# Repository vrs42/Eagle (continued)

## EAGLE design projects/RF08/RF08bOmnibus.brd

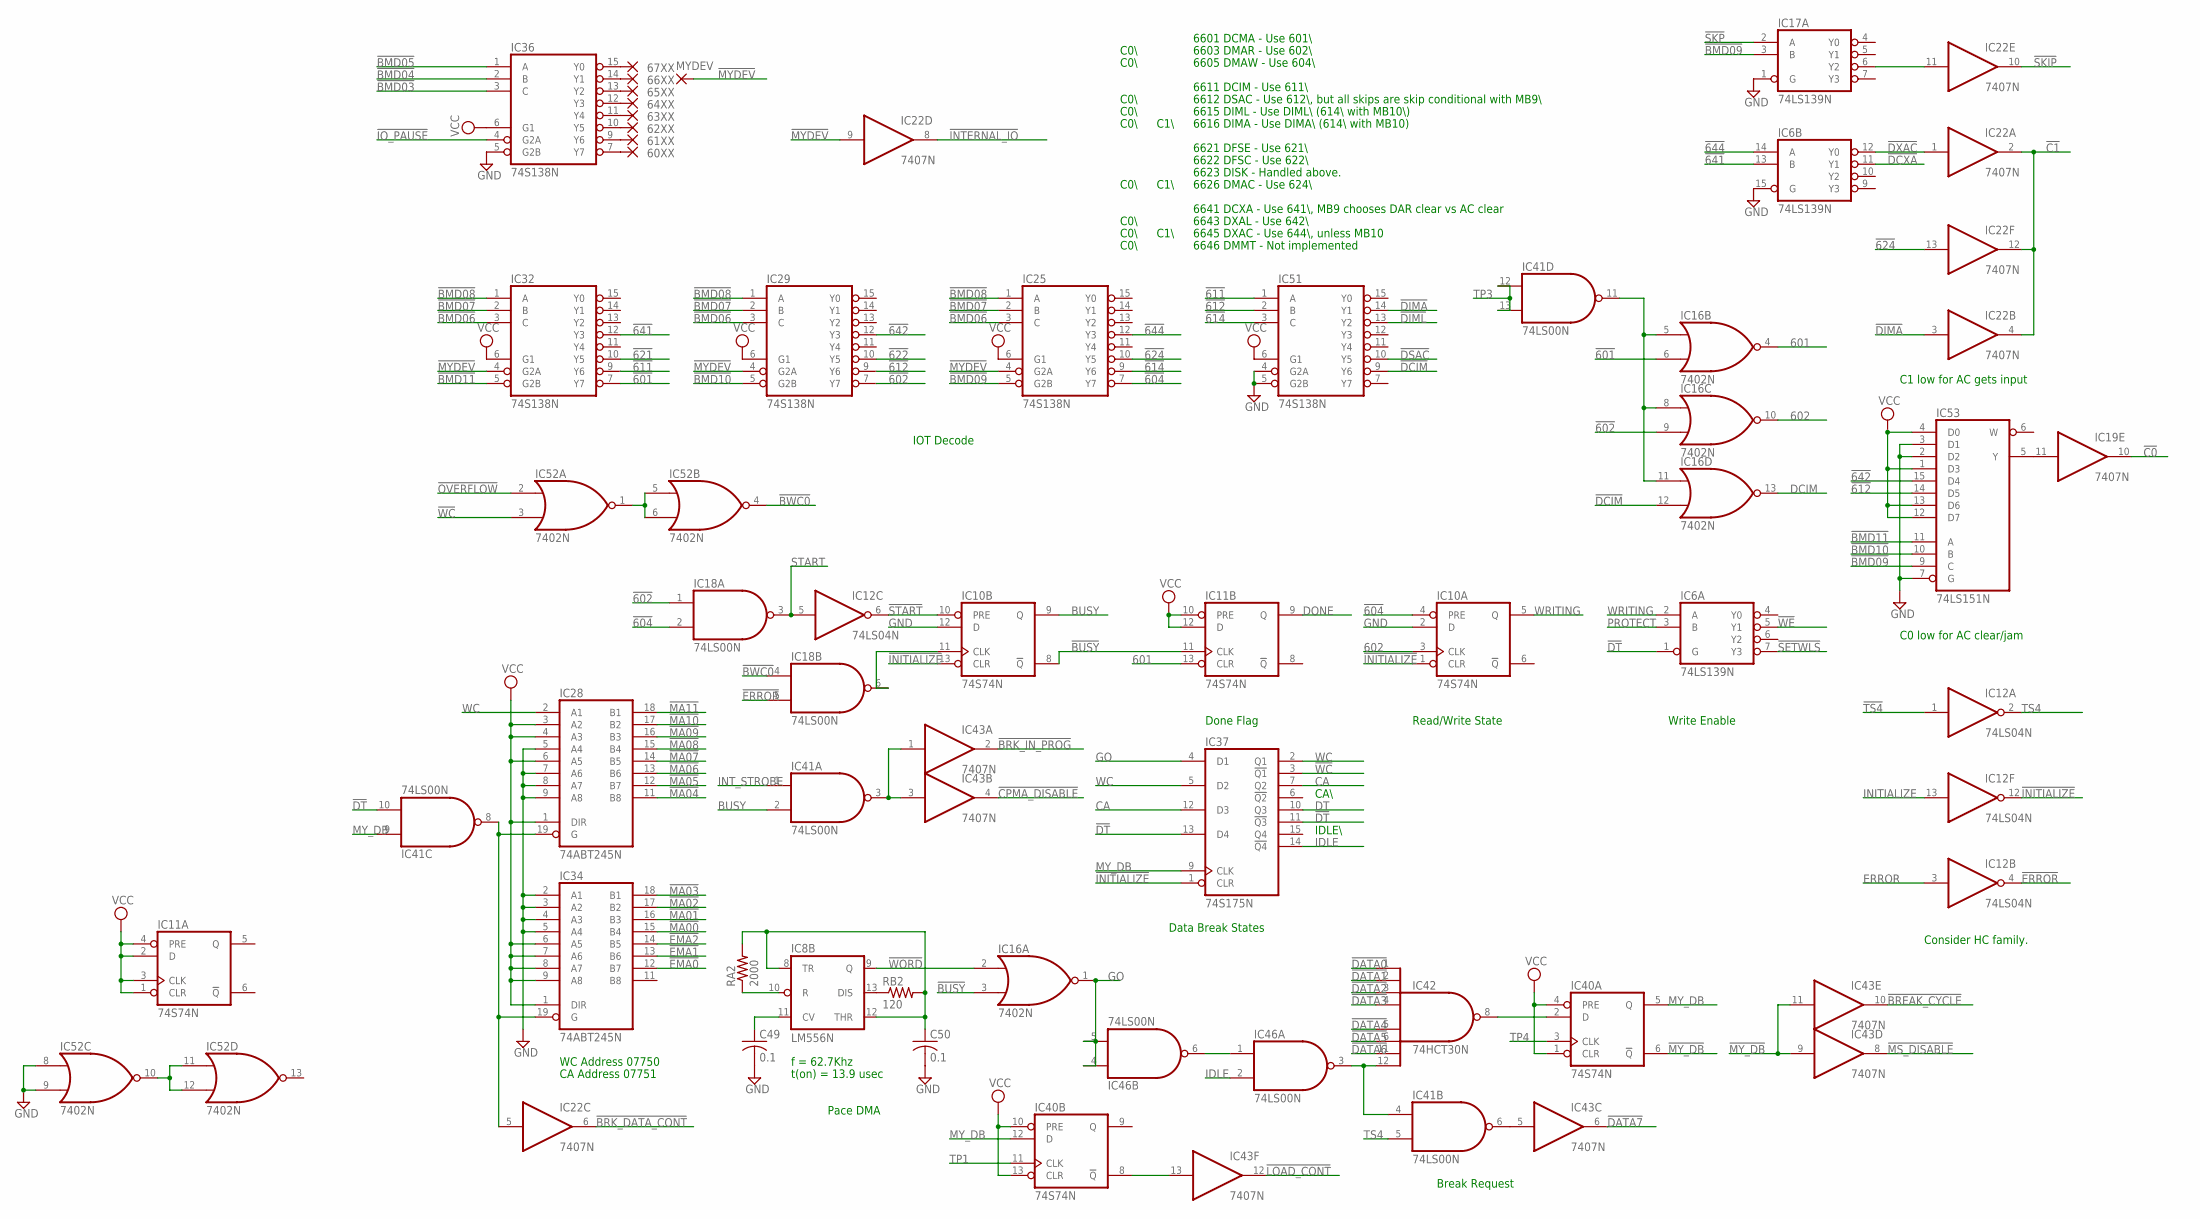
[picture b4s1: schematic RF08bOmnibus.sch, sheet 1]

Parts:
60XX, 61XX, 62XX, 63XX, 64XX, 65XX, 66XX, 67XX: 1,6/0,8
C49, C50: 0.1; C050-025X075
IC6, IC17: 74LS139N; DIL16
IC8: LM556N; DIL14
IC10, IC11, IC40: 74S74N; DIL14
IC12: 74LS04N; DIL14
IC16, IC52: 7402N; DIL14
IC18, IC41, IC46: 74LS00N; DIL14
IC19, IC22, IC43: 7407N; DIL14
IC25, IC29, IC32, IC36, IC51: 74S138N; DIL16
IC28, IC34: 74ABT245N; DIL20
IC37: 74S175N; DIL16
IC42: 74HCT30N; DIL14
IC53: 74LS151N; DIL16
MYDEV: 1,6/0,8
RA2: 2000; 0207/10
RB2: 120; 0207/10

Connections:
601: IC11.13 (CLR), IC16.4 (O); also elsewhere on the board
602: IC10.3 (CLK), IC16.10 (O)
!601: IC16.6 (I1), IC32.7 (Y7); also elsewhere on the board
!602: IC16.9 (I1), IC18.1 (I0), IC29.7 (Y7)
!604: IC10.4 (PRE), IC18.2 (I1), IC25.7 (Y7)
!611: IC32.9 (Y6), IC51.1 (A)
!612: IC29.9 (Y6), IC51.2 (B), IC53.14 (D5)
!614: IC25.9 (Y6), IC51.3 (C)
!621: IC32.10 (Y5); also elsewhere on the board
!622: IC29.10 (Y5); also elsewhere on the board
!624: IC22.13 (I), IC25.10 (Y5); also elsewhere on the board
!641: IC6.13 (B), IC32.12 (Y3)
!642: IC29.12 (Y3), IC53.15 (D4); also elsewhere on the board
!644: IC6.14 (A), IC25.12 (Y3)
!BMD03: IC36.3 (C); also elsewhere on the board
!BMD04: IC36.2 (B); also elsewhere on the board
!BMD05: IC36.1 (A); also elsewhere on the board
!BMD06: IC25.3 (C), IC29.3 (C), IC32.3 (C); also elsewhere on the board
!BMD07: IC25.2 (B), IC29.2 (B), IC32.2 (B); also elsewhere on the board
!BMD08: IC25.1 (A), IC29.1 (A), IC32.1 (A); also elsewhere on the board
!BMD09: IC17.3 (B), IC25.5 (G2B), IC53.9 (C); also elsewhere on the board
!BMD10: IC29.5 (G2B), IC53.10 (B); also elsewhere on the board
!BMD11: IC32.5 (G2B), IC53.11 (A); also elsewhere on the board
!BREAK_CYCLE: IC43.10 (O); also elsewhere on the board
!BRK_DATA_CONT: IC22.6 (O); also elsewhere on the board
!BRK_IN_PROG: IC43.2 (O); also elsewhere on the board
!BUSY: IC10.8 (!Q), IC11.11 (CLK), IC16.3 (I1)
!BWC0: IC18.4 (I0), IC52.4 (O); also elsewhere on the board
!C0: IC19.10 (O); also elsewhere on the board
!C1: IC22.2 (O), IC22.4 (O), IC22.12 (O); also elsewhere on the board
!CPMA_DISABLE: IC43.4 (O); also elsewhere on the board
!DATA0: IC42.1 (I0); also elsewhere on the board
!DATA1: IC42.2 (I1); also elsewhere on the board
!DATA2: IC42.3 (I2); also elsewhere on the board
!DATA3: IC42.4 (I3); also elsewhere on the board
!DATA4: IC42.5 (I4); also elsewhere on the board
!DATA5: IC42.6 (I5); also elsewhere on the board
!DATA6: IC42.11 (I6); also elsewhere on the board
!DATA7: IC43.6 (O); also elsewhere on the board
!DCIM: IC16.12 (I1), IC51.9 (Y6)
!DCXA: IC6.11 (Y1); also elsewhere on the board
!DIMA: IC22.3 (I), IC51.14 (Y1); also elsewhere on the board
!DIML: IC51.13 (Y2); also elsewhere on the board
!DSAC: IC51.10 (Y5); also elsewhere on the board
!DT: IC6.1 (G), IC37.11 (!Q3), IC37.13 (D4), IC41.10 (I1); also elsewhere on the board
!DXAC: IC6.12 (Y0), IC22.1 (I); also elsewhere on the board
!EMA0: IC34.12 (B7); also elsewhere on the board
!EMA1: IC34.13 (B6); also elsewhere on the board
!EMA2: IC34.14 (B5); also elsewhere on the board
!ERROR: IC12.4 (O), IC18.5 (I1)
!INITIALIZE: IC10.1 (CLR), IC10.13 (CLR), IC12.12 (O), IC37.1 (CLR); also elsewhere on the board
!INTERNAL_IO: IC22.8 (O); also elsewhere on the board
!IO_PAUSE: IC36.4 (G2A); also elsewhere on the board
!LOAD_CONT: IC43.12 (O); also elsewhere on the board
!MA00: IC34.15 (B4); also elsewhere on the board
!MA01: IC34.16 (B3); also elsewhere on the board
!MA02: IC34.17 (B2); also elsewhere on the board
!MA03: IC34.18 (B1); also elsewhere on the board
!MA04: IC28.11 (B8); also elsewhere on the board
!MA05: IC28.12 (B7); also elsewhere on the board
!MA06: IC28.13 (B6); also elsewhere on the board
!MA07: IC28.14 (B5); also elsewhere on the board
!MA08: IC28.15 (B4); also elsewhere on the board
!MA09: IC28.16 (B3); also elsewhere on the board
!MA10: IC28.17 (B2); also elsewhere on the board
!MA11: IC28.18 (B1); also elsewhere on the board
!MS_DISABLE: IC43.8 (O); also elsewhere on the board
!MYDEV: IC22.9 (I), IC25.4 (G2A), IC29.4 (G2A), IC32.4 (G2A), MYDEV.1
!MY_DB: IC40.6 (!Q), IC43.9 (I), IC43.11 (I); also elsewhere on the board
!OVERFLOW: IC52.2 (I0); also elsewhere on the board
!SETWLS: IC6.7 (Y3); also elsewhere on the board
!SKIP: IC22.10 (O); also elsewhere on the board
!SKP: IC17.2 (A); also elsewhere on the board
!START: IC10.10 (PRE), IC12.6 (O); also elsewhere on the board
!TS4: IC12.1 (I); also elsewhere on the board
!WC: IC37.3 (!Q1), IC52.3 (I1)
!WE: IC6.5 (Y1); also elsewhere on the board
!WORD: IC8.9 (Q), IC16.2 (I0)
BUSY: IC10.9 (Q), IC41.2 (I1); also elsewhere on the board
CA: IC37.7 (Q2), IC37.12 (D3); also elsewhere on the board
DCIM: IC16.13 (O); also elsewhere on the board
DONE: IC11.9 (Q); also elsewhere on the board
DT: IC37.10 (Q3); also elsewhere on the board
ERROR: IC12.3 (I); also elsewhere on the board
GND: C49.2, C50.2, IC6.8 (GND), IC6.15 (G), IC10.2 (D), IC10.7 (GND), IC10.12 (D), IC11.7 (GND), IC12.7 (GND), IC16.7 (GND), IC17.1 (G), IC17.8 (GND), IC18.7 (GND), IC19.7 (GND), IC22.7 (GND), IC25.8 (GND), IC28.5 (A4), IC28.7 (A6), IC28.8 (A7), IC28.9 (A8), IC28.10 (GND), IC29.8 (GND), IC32.8 (GND), IC34.2 (A1), IC34.3 (A2), IC34.4 (A3), IC34.5 (A4), IC34.10 (GND), IC36.5 (G2B), IC36.8 (GND), IC37.8 (GND), IC40.7 (GND), IC41.7 (GND), IC42.7 (GND), IC43.7 (GND), IC46.7 (GND), IC51.4 (G2A), IC51.5 (G2B), IC51.8 (GND), IC52.7 (GND), IC52.8 (I0), IC52.9 (I1), IC53.2 (D2), IC53.3 (D1), IC53.7 (G), IC53.8 (GND); also elsewhere on the board
GO: IC16.1 (O), IC37.4 (D1), IC46.4 (I0), IC46.5 (I1)
IDLE: IC37.14 (!Q4), IC46.2 (I1)
INITIALIZE: IC12.13 (I); also elsewhere on the board
INT_STROBE: IC41.1 (I0); also elsewhere on the board
MY_DB: IC37.9 (CLK), IC40.5 (Q), IC40.12 (D), IC41.9 (I0)
unnamed: 60XX.1, IC36.7 (Y7)
unnamed: IC19.11 (I), IC53.5 (Y)
unnamed: 61XX.1, IC36.9 (Y6)
unnamed: 62XX.1, IC36.10 (Y5)
unnamed: 63XX.1, IC36.11 (Y4)
unnamed: 64XX.1, IC36.12 (Y3)
unnamed: 65XX.1, IC36.13 (Y2)
unnamed: 67XX.1, IC36.15 (Y0)
unnamed: 66XX.1, IC36.14 (Y1)
unnamed: IC10.11 (CLK), IC18.6 (O)
unnamed: IC46.1 (I0), IC46.6 (O)
unnamed: IC17.6 (Y2), IC22.11 (I)
unnamed: IC16.5 (I0), IC16.8 (I0), IC16.11 (I0), IC41.11 (O)
unnamed: IC40.8 (!Q), IC43.13 (I)
unnamed: IC41.3 (O), IC43.1 (I), IC43.3 (I)
unnamed: IC41.6 (O), IC43.5 (I)
unnamed: IC40.2 (D), IC42.8 (O)
unnamed: IC22.5 (I), IC28.19 (G), IC34.19 (G), IC41.8 (O)
unnamed: IC52.1 (O), IC52.5 (I0), IC52.6 (I1)
unnamed: IC8.13 (DIS), RB2.1
unnamed: C49.1, IC8.11 (CV)
unnamed: C50.1, IC8.8 (TR), IC8.12 (THR), RA2.2, RB2.2
unnamed: IC8.10 (R), RA2.1
unnamed: IC52.10 (O), IC52.11 (I0), IC52.12 (I1)
unnamed: IC41.4 (I0), IC42.12 (I7), IC46.3 (O)
PROTECT: IC6.3 (B); also elsewhere on the board
START: IC12.5 (I), IC18.3 (O)
TP1: IC40.11 (CLK); also elsewhere on the board
TP3: IC41.12 (I0), IC41.13 (I1); also elsewhere on the board
TP4: IC40.3 (CLK); also elsewhere on the board
TS4: IC12.2 (O), IC41.5 (I1)
VCC: IC6.16 (VCC), IC10.14 (VCC), IC11.1 (CLR), IC11.2 (D), IC11.3 (CLK), IC11.4 (PRE), IC11.10 (PRE), IC11.12 (D), IC11.14 (VCC), IC12.14 (VCC), IC16.14 (VCC), IC17.16 (VCC), IC18.14 (VCC), IC19.14 (VCC), IC22.14 (VCC), IC25.6 (G1), IC25.16 (VCC), IC28.1 (DIR), IC28.3 (A2), IC28.4 (A3), IC28.6 (A5), IC28.20 (VCC), IC29.6 (G1), IC29.16 (VCC), IC32.6 (G1), IC32.16 (VCC), IC34.1 (DIR), IC34.6 (A5), IC34.7 (A6), IC34.8 (A7), IC34.9 (A8), IC34.20 (VCC), IC36.6 (G1), IC36.16 (VCC), IC37.16 (VCC), IC40.1 (CLR), IC40.4 (PRE), IC40.10 (PRE), IC40.13 (CLR), IC40.14 (VCC), IC41.14 (VCC), IC42.14 (VCC), IC43.14 (VCC), IC46.14 (VCC), IC51.6 (G1), IC51.16 (VCC), IC52.14 (VCC), IC53.1 (D3), IC53.4 (D0), IC53.12 (D7), IC53.13 (D6), IC53.16 (VCC); also elsewhere on the board
WC: IC28.2 (A1), IC37.2 (Q1), IC37.5 (D2)
WRITING: IC6.2 (A), IC10.5 (Q); also elsewhere on the board

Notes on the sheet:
6601 DCMA - Use 601\\
6603 DMAR - Use 602\\
6605 DMAW - Use 604\\
6611 DCIM - Use 611\\
6612 DSAC - Use 612\\, but all skips are skip conditional with MB9\\
6615 DIML - Use DIML\\ (614\\ with MB10\\)
6616 DIMA - Use DIMA\\ (614\\ with MB10)
6621 DFSE - Use 621\\
6622 DFSC - Use 622\\
6623 DISK - Handled above.
6626 DMAC - Use 624\\
6641 DCXA - Use 641\\, MB9 chooses DAR clear vs AC clear
6643 DXAL - Use 642\\
6645 DXAC - Use 644\\, unless MB10
6646 DMMT - Not implemented
IOT Decode
WC Address 07750
Break Request
Done Flag
Read/Write State
Write Enable
Consider HC family.
CA Address 07751
Data Break States
f = 62.7Khz
t(on) = 13.9 usec
Pace DMA
CA\\
IDLE\\
C0 low for AC clear/jam
C1 low for AC gets input
C0\\
C1\\

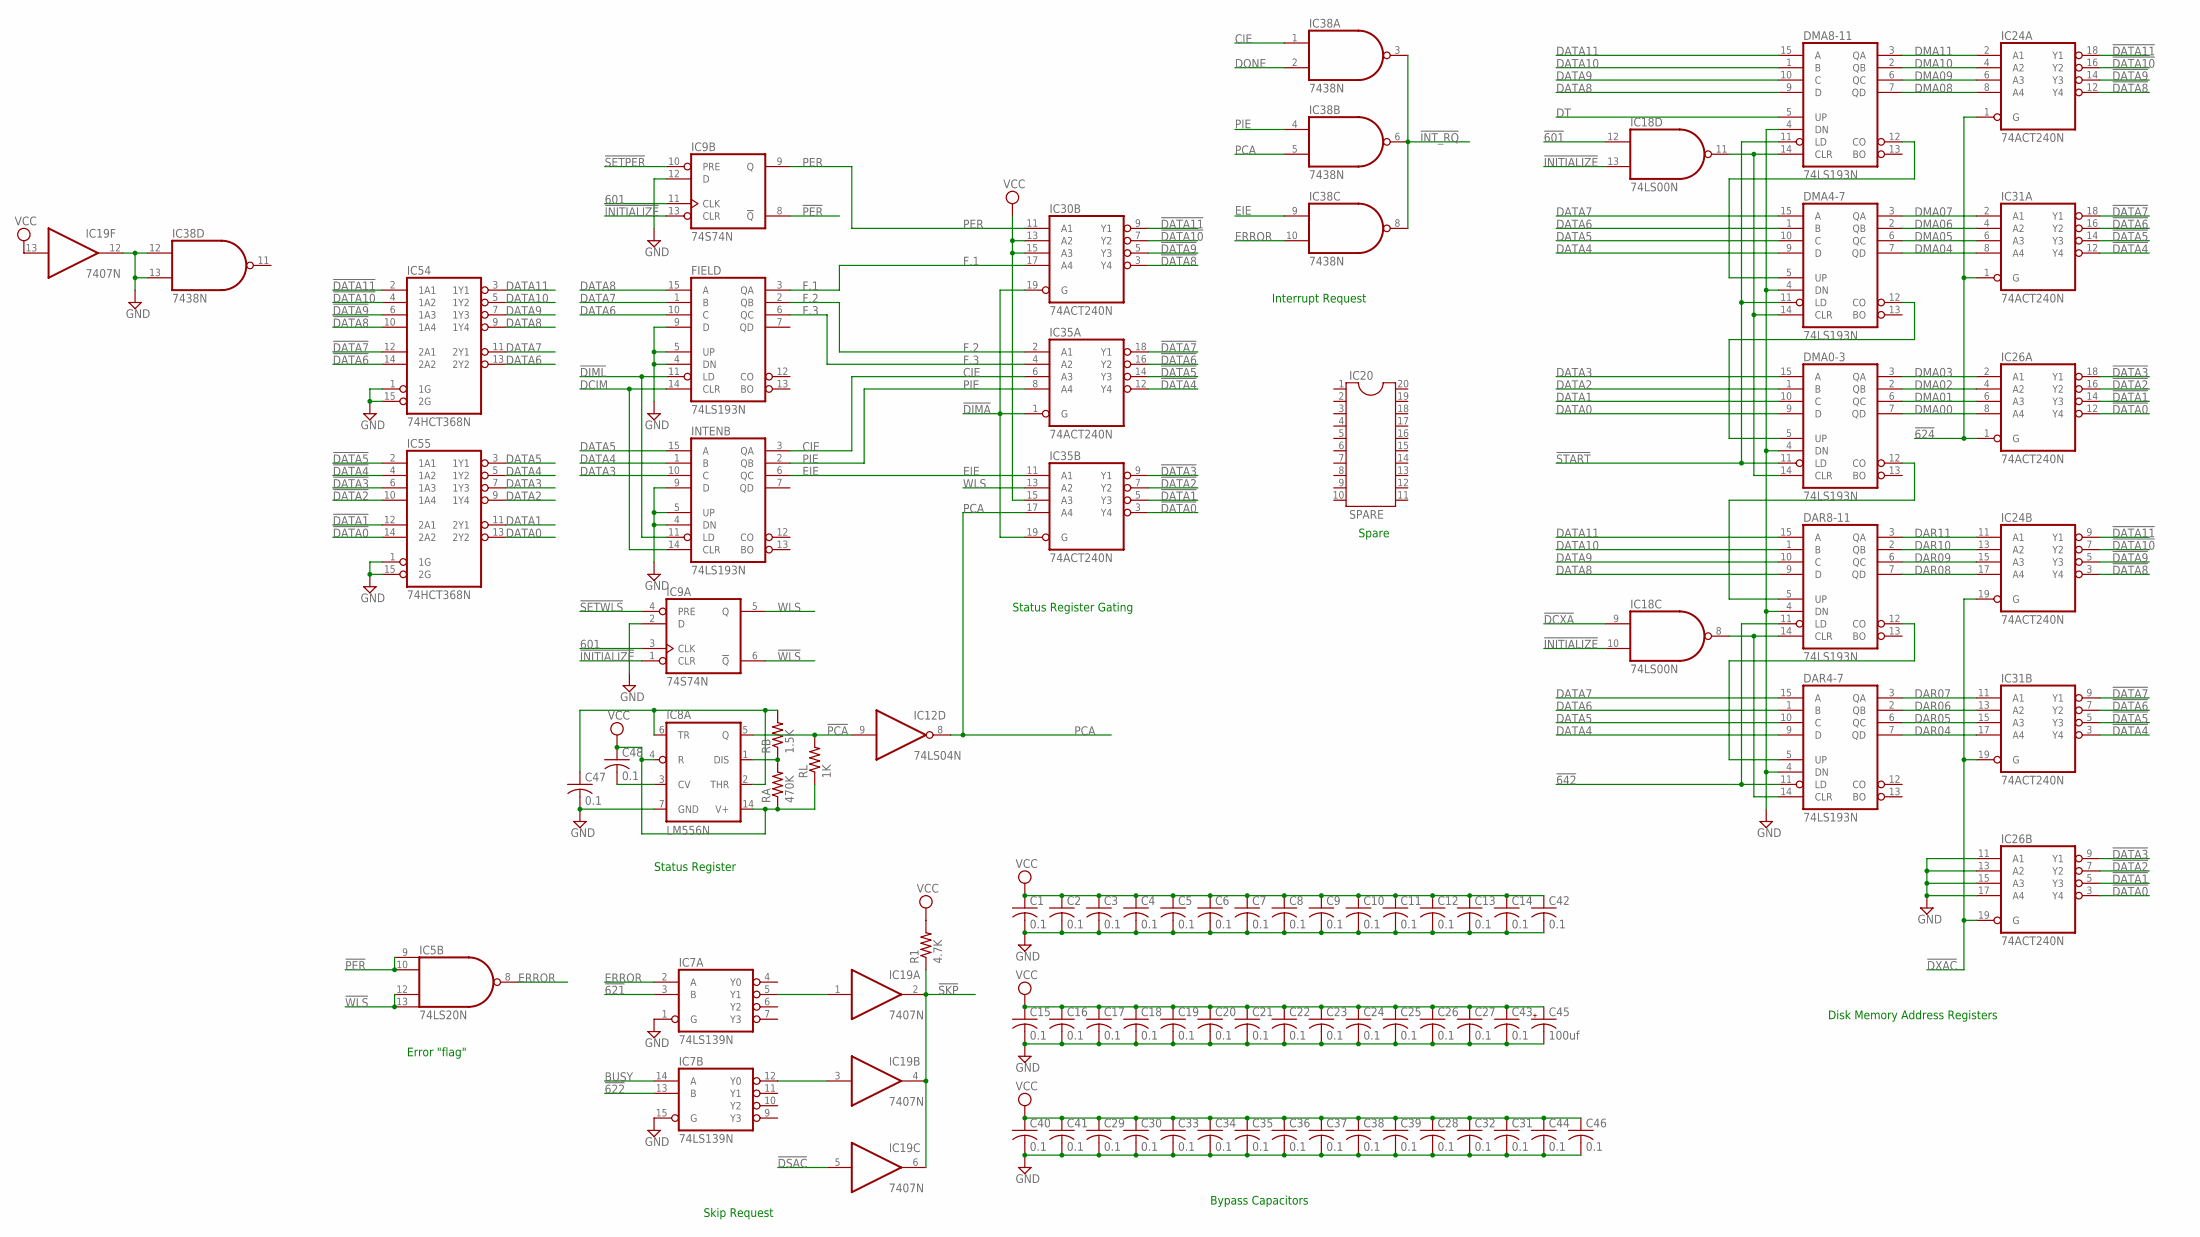
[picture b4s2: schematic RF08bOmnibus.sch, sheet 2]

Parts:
C1, C2, C3, C4, C5, C6, C7, C8, C9, C10, C11, C12, C13, C14, C15, C16, C17, C18, C19, C20, C21, C22, C23, C24, C25, C26, C27, C28, C29, C30, C31, C32, C33, C34, C35, C36, C37, C38, C39, C40, C41, C42, C43, C44, C46, C47, C48: 0.1; C050-025X075
C45: 100uf; E22-6
DAR4-7, DAR8-11: 74LS193N; DIL16
DMA0-3, DMA4-7, DMA8-11: 74LS193N; DIL16
FIELD: 74LS193N; DIL16
IC5: 74LS20N; DIL14
IC7: 74LS139N; DIL16
IC8: LM556N; DIL14
IC9: 74S74N; DIL14
IC12: 74LS04N; DIL14
IC18: 74LS00N; DIL14
IC19: 7407N; DIL14
IC20: SPARE; DIL20
IC24, IC26, IC30, IC31, IC35: 74ACT240N; DIL20
IC38: 7438N; DIL14
IC54, IC55: 74HCT368N; DIL16
INTENB: 74LS193N; DIL16
R1: 4.7K; 0207/10
RA: 470K; 0207/10
RB: 1.5K; 0207/10
RL: 1K; 0207/10

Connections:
601: IC9.3 (CLK), IC9.11 (CLK); also elsewhere on the board
!601: IC18.12 (I0); also elsewhere on the board
!621: IC7.3 (B); also elsewhere on the board
!622: IC7.13 (B); also elsewhere on the board
!624: IC24.1 (G), IC26.1 (G), IC31.1 (G); also elsewhere on the board
!642: DAR4-7.11 (LD), DAR8-11.11 (LD); also elsewhere on the board
!DATA0: IC26.3 (Y4), IC26.12 (Y4), IC35.3 (Y4), IC55.14 (2A2); also elsewhere on the board
!DATA1: IC26.5 (Y3), IC26.14 (Y3), IC35.5 (Y3), IC55.12 (2A1); also elsewhere on the board
!DATA2: IC26.7 (Y2), IC26.16 (Y2), IC35.7 (Y2), IC55.10 (1A4); also elsewhere on the board
!DATA3: IC26.9 (Y1), IC26.18 (Y1), IC35.9 (Y1), IC55.6 (1A3); also elsewhere on the board
!DATA4: IC31.3 (Y4), IC31.12 (Y4), IC35.12 (Y4), IC55.4 (1A2); also elsewhere on the board
!DATA5: IC31.5 (Y3), IC31.14 (Y3), IC35.14 (Y3), IC55.2 (1A1); also elsewhere on the board
!DATA6: IC31.7 (Y2), IC31.16 (Y2), IC35.16 (Y2), IC54.14 (2A2); also elsewhere on the board
!DATA7: IC31.9 (Y1), IC31.18 (Y1), IC35.18 (Y1), IC54.12 (2A1); also elsewhere on the board
!DATA8: IC24.3 (Y4), IC24.12 (Y4), IC30.3 (Y4), IC54.10 (1A4); also elsewhere on the board
!DATA9: IC24.5 (Y3), IC24.14 (Y3), IC30.5 (Y3), IC54.6 (1A3); also elsewhere on the board
!DATA10: IC24.7 (Y2), IC24.16 (Y2), IC30.7 (Y2), IC54.4 (1A2); also elsewhere on the board
!DATA11: IC24.9 (Y1), IC24.18 (Y1), IC30.9 (Y1), IC54.2 (1A1); also elsewhere on the board
!DCXA: IC18.9 (I0); also elsewhere on the board
!DIMA: IC30.19 (G), IC35.1 (G), IC35.19 (G); also elsewhere on the board
!DIML: FIELD.11 (LD), INTENB.11 (LD); also elsewhere on the board
!DSAC: IC19.5 (I); also elsewhere on the board
!DXAC: IC24.19 (G), IC26.19 (G), IC31.19 (G); also elsewhere on the board
!INITIALIZE: IC9.1 (CLR), IC9.13 (CLR), IC18.10 (I1), IC18.13 (I1); also elsewhere on the board
!INT_RQ: IC38.3 (O), IC38.6 (O), IC38.8 (O)
!PCA: IC8.5 (Q), IC12.9 (I), RL.2
!PER: IC5.9 (I0), IC5.10 (I1), IC9.8 (!Q)
!SETPER: IC9.10 (PRE); also elsewhere on the board
!SETWLS: IC9.4 (PRE); also elsewhere on the board
!SKP: IC19.2 (O), IC19.4 (O), IC19.6 (O), R1.1; also elsewhere on the board
!START: DMA0-3.11 (LD), DMA4-7.11 (LD), DMA8-11.11 (LD); also elsewhere on the board
!WLS: IC5.12 (I2), IC5.13 (I3), IC9.6 (!Q)
BUSY: IC7.14 (A); also elsewhere on the board
CIE: IC35.6 (A3), IC38.1 (I0), INTENB.3 (QA); also elsewhere on the board
DAR04: DAR4-7.7 (QD), IC31.17 (A4); also elsewhere on the board
DAR05: DAR4-7.6 (QC), IC31.15 (A3); also elsewhere on the board
DAR06: DAR4-7.2 (QB), IC31.13 (A2); also elsewhere on the board
DAR07: DAR4-7.3 (QA), IC31.11 (A1); also elsewhere on the board
DAR08: DAR8-11.7 (QD), IC24.17 (A4); also elsewhere on the board
DAR09: DAR8-11.6 (QC), IC24.15 (A3); also elsewhere on the board
DAR10: DAR8-11.2 (QB), IC24.13 (A2); also elsewhere on the board
DAR11: DAR8-11.3 (QA), IC24.11 (A1); also elsewhere on the board
DATA0: DMA0-3.9 (D), IC55.13 (2Y2)
DATA1: DMA0-3.10 (C), IC55.11 (2Y1)
DATA2: DMA0-3.1 (B), IC55.9 (1Y4)
DATA3: DMA0-3.15 (A), IC55.7 (1Y3), INTENB.10 (C)
DATA4: DAR4-7.9 (D), DMA4-7.9 (D), IC55.5 (1Y2), INTENB.1 (B)
DATA5: DAR4-7.10 (C), DMA4-7.10 (C), IC55.3 (1Y1), INTENB.15 (A)
DATA6: DAR4-7.1 (B), DMA4-7.1 (B), FIELD.10 (C), IC54.13 (2Y2)
DATA7: DAR4-7.15 (A), DMA4-7.15 (A), FIELD.1 (B), IC54.11 (2Y1)
DATA8: DAR8-11.9 (D), DMA8-11.9 (D), FIELD.15 (A), IC54.9 (1Y4)
DATA9: DAR8-11.10 (C), DMA8-11.10 (C), IC54.7 (1Y3)
DATA10: DAR8-11.1 (B), DMA8-11.1 (B), IC54.5 (1Y2)
DATA11: DAR8-11.15 (A), DMA8-11.15 (A), IC54.3 (1Y1)
DCIM: FIELD.14 (CLR), INTENB.14 (CLR); also elsewhere on the board
DMA00: DMA0-3.7 (QD), IC26.8 (A4); also elsewhere on the board
DMA01: DMA0-3.6 (QC), IC26.6 (A3); also elsewhere on the board
DMA02: DMA0-3.2 (QB), IC26.4 (A2); also elsewhere on the board
DMA03: DMA0-3.3 (QA), IC26.2 (A1); also elsewhere on the board
DMA04: DMA4-7.7 (QD), IC31.8 (A4); also elsewhere on the board
DMA05: DMA4-7.6 (QC), IC31.6 (A3); also elsewhere on the board
DMA06: DMA4-7.2 (QB), IC31.4 (A2); also elsewhere on the board
DMA07: DMA4-7.3 (QA), IC31.2 (A1); also elsewhere on the board
DMA08: DMA8-11.7 (QD), IC24.8 (A4); also elsewhere on the board
DMA09: DMA8-11.6 (QC), IC24.6 (A3); also elsewhere on the board
DMA10: DMA8-11.2 (QB), IC24.4 (A2); also elsewhere on the board
DMA11: DMA8-11.3 (QA), IC24.2 (A1); also elsewhere on the board
DONE: IC38.2 (I1); also elsewhere on the board
DT: DMA8-11.5 (UP); also elsewhere on the board
EIE: IC35.11 (A1), IC38.9 (I0), INTENB.6 (QC); also elsewhere on the board
ERROR: IC5.8 (O), IC7.2 (A), IC38.10 (I1); also elsewhere on the board
F.1: FIELD.3 (QA), IC30.17 (A4); also elsewhere on the board
F.2: FIELD.2 (QB), IC35.2 (A1); also elsewhere on the board
F.3: FIELD.6 (QC), IC35.4 (A2); also elsewhere on the board
GND: C1.2, C2.2, C3.2, C4.2, C5.2, C6.2, C7.2, C8.2, C9.2, C10.2, C11.2, C12.2, C13.2, C14.2, C15.2, C16.2, C17.2, C18.2, C19.2, C20.2, C21.2, C22.2, C23.2, C24.2, C25.2, C26.2, C27.2, C28.2, C29.2, C30.2, C31.2, C32.2, C33.2, C34.2, C35.2, C36.2, C37.2, C38.2, C39.2, C40.2, C41.2, C42.2, C43.2, C44.2, C45.-, C46.2, C47.2, DAR4-7.4 (DN), DAR4-7.8 (GND), DAR8-11.4 (DN), DAR8-11.8 (GND), DMA0-3.4 (DN), DMA0-3.8 (GND), DMA4-7.4 (DN), DMA4-7.8 (GND), DMA8-11.4 (DN), DMA8-11.8 (GND), FIELD.4 (DN), FIELD.5 (UP), FIELD.8 (GND), FIELD.9 (D), IC5.7 (GND), IC7.1 (G), IC7.8 (GND), IC7.15 (G), IC8.7 (GND), IC9.2 (D), IC9.7 (GND), IC9.12 (D), IC12.7 (GND), IC18.7 (GND), IC19.7 (GND), IC19.12 (O), IC24.10 (GND), IC26.10 (GND), IC26.11 (A1), IC26.13 (A2), IC26.15 (A3), IC26.17 (A4), IC30.10 (GND), IC31.10 (GND), IC35.10 (GND), IC38.7 (GND), IC38.12 (I0), IC38.13 (I1), IC54.1 (1G), IC54.8 (GND), IC54.15 (2G), IC55.1 (1G), IC55.8 (GND), IC55.15 (2G), INTENB.4 (DN), INTENB.5 (UP), INTENB.8 (GND), INTENB.9 (D); also elsewhere on the board
unnamed: DMA0-3.5 (UP), DMA4-7.12 (CO)
unnamed: DAR4-7.14 (CLR), DAR8-11.14 (CLR), IC18.8 (O)
unnamed: DMA4-7.5 (UP), DMA8-11.12 (CO)
unnamed: DAR8-11.5 (UP), DMA0-3.12 (CO)
unnamed: DMA0-3.14 (CLR), DMA4-7.14 (CLR), DMA8-11.14 (CLR), IC18.11 (O)
unnamed: DAR4-7.5 (UP), DAR8-11.12 (CO)
unnamed: IC7.5 (Y1), IC19.1 (I)
unnamed: IC8.1 (DIS), RA.2, RB.1
unnamed: C47.1, IC8.2 (THR), IC8.6 (TR), RB.2
unnamed: IC7.12 (Y0), IC19.3 (I)
unnamed: C48.2, IC8.3 (CV)
PCA: IC12.8 (O), IC35.17 (A4), IC38.5 (I1)
PER: IC9.9 (Q), IC30.11 (A1); also elsewhere on the board
PIE: IC35.8 (A4), IC38.4 (I0), INTENB.2 (QB); also elsewhere on the board
VCC: C1.1, C2.1, C3.1, C4.1, C5.1, C6.1, C7.1, C8.1, C9.1, C10.1, C11.1, C12.1, C13.1, C14.1, C15.1, C16.1, C17.1, C18.1, C19.1, C20.1, C21.1, C22.1, C23.1, C24.1, C25.1, C26.1, C27.1, C28.1, C29.1, C30.1, C31.1, C32.1, C33.1, C34.1, C35.1, C36.1, C37.1, C38.1, C39.1, C40.1, C41.1, C42.1, C43.1, C44.1, C45.+, C46.1, C48.1, DAR4-7.16 (VCC), DAR8-11.16 (VCC), DMA0-3.16 (VCC), DMA4-7.16 (VCC), DMA8-11.16 (VCC), FIELD.16 (VCC), IC5.14 (VCC), IC7.16 (VCC), IC8.4 (R), IC8.14 (V+), IC9.14 (VCC), IC12.14 (VCC), IC18.14 (VCC), IC19.13 (I), IC19.14 (VCC), IC24.20 (VCC), IC26.20 (VCC), IC30.13 (A2), IC30.15 (A3), IC30.20 (VCC), IC31.20 (VCC), IC35.15 (A3), IC35.20 (VCC), IC38.14 (VCC), IC54.16 (VCC), IC55.16 (VCC), INTENB.16 (VCC), R1.2, RA.1, RL.1; also elsewhere on the board
WLS: IC9.5 (Q), IC35.13 (A2); also elsewhere on the board

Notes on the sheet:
Disk Memory Address Registers
Status Register
Status Register Gating
Interrupt Request
Error "flag"
Skip Request
Spare
Bypass Capacitors
